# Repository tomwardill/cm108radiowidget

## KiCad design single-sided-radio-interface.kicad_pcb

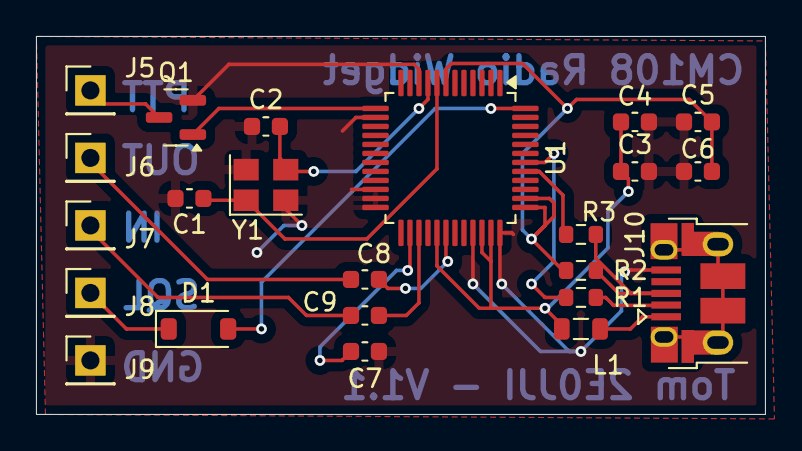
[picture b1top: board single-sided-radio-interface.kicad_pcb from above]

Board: 2 copper layers, 40.5 x 21.0 mm, 23 parts (0 on the bottom side), 16 nets.

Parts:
C1, C2: 20p; C_0603_1608Metric
C3, C5: 100n; C_0603_1608Metric
C4, C6, C7: 4.7u; C_0603_1608Metric
C8, C9: 1u; C_0603_1608Metric
D1: B5819W(BAT46W); D_SOD-123
J5: PTT; PinHeader_1x01_P2.54mm_Vertical
J6: AUDIO_OUT; PinHeader_1x01_P2.54mm_Vertical
J7: AUDIO_IN; PinHeader_1x01_P2.54mm_Vertical
J8: SQUELCH; PinHeader_1x01_P2.54mm_Vertical
J9: GND; PinHeader_1x01_P2.54mm_Vertical
J10: USB_B_Micro; USB_Micro-B_Amphenol_10103594-0001LF_Horizontal
L1: 10u; L_0805_2012Metric
Q1: BSS138; SOT-23
R1, R3: 22; R_0603_1608Metric
R2: 1.5k; R_0603_1608Metric
U1: CM108AH; LQFP-48_7x7mm_P0.5mm
Y1: 12M; Crystal_SMD_3225-4Pin_3.2x2.5mm

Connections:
+3V3: C5.1, C6.1, R2.2, U1.7 (PWRSEL), U1.37 (REGV), U1.38 (MSEL)
AUDIO_IN: C9.1, J7.1
AUDIO_OUT: C8.1, J6.1
GND: C1.2, C2.1, C3.2, C4.2, C5.2, C6.2, C7.2, J9.1, J10.5 (GND), Q1.2 (S), U1.10 (MODE), U1.14 (DVSS), U1.22 (ADSEL), U1.23 (TEST), U1.24 (AVSS), U1.33 (AVSS), U1.36 (DVSS), Y1.2, Y1.4
NET-(U1-BGREF): C7.1, U1.26
NET-(U1-USBDP): R3.1, U1.41
unnamed: D1.2, U1.48
unnamed: Q1.1, U1.13
unnamed: C8.2, U1.30
unnamed: C9.2, U1.27
unnamed: R1.1, U1.42
unnamed: C1.1, U1.8, Y1.1
unnamed: C2.2, U1.9, Y1.3
PTT: J5.1, Q1.3 (D)
SQUELCH: D1.1 (K), J8.1
VCC: C3.1, C4.1, L1.1, U1.29 (AVDD), U1.34 (AVDD), U1.35 (DVDD)

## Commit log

2024-12-18 V1.0
2024-12-18 V1.1 - smaller board
2025-01-01 Move L1 lable to correct place
